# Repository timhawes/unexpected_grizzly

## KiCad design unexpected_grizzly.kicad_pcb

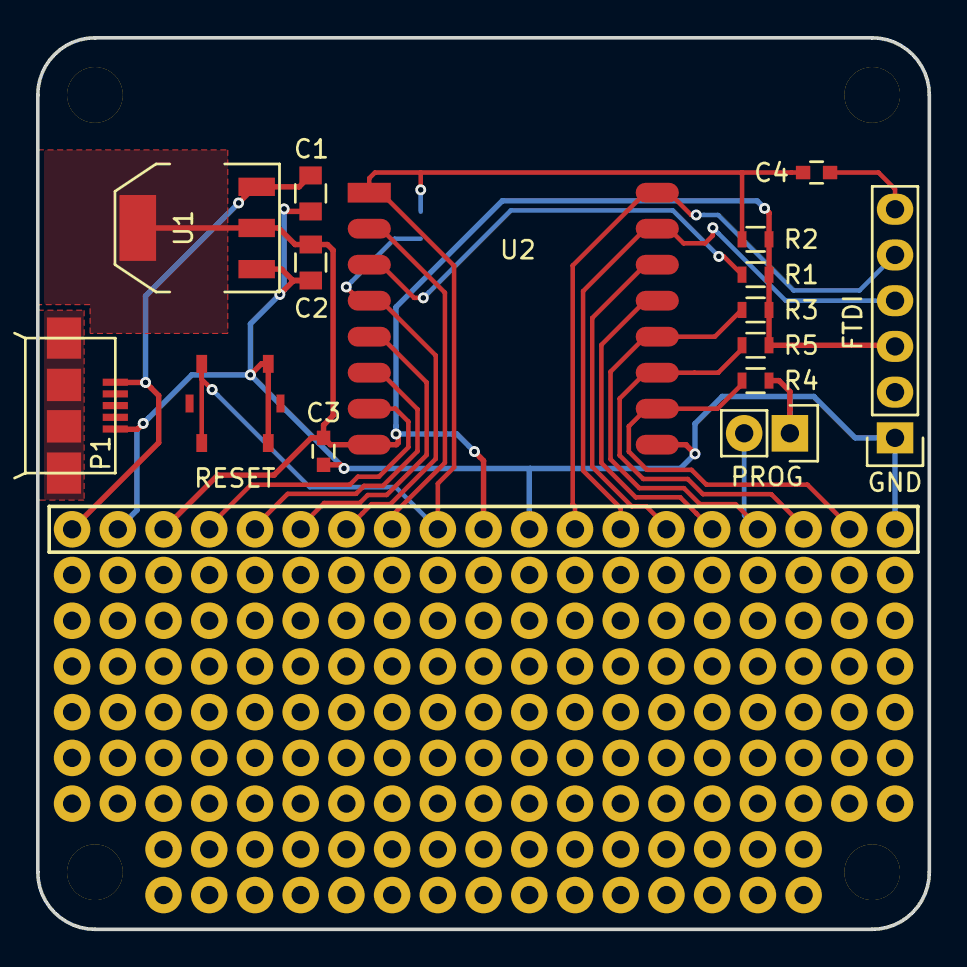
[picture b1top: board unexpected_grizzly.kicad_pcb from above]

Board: 2 copper layers, 49.5 x 49.5 mm, 17 parts (1 on the bottom side), 18 nets.

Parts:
C1, C2: 10uF; C_0805
C3, C4: 0.1uF; C_0603
JP1: PROG; Pin_Header_Straight_1x02
JP2: WAKE; R_0603
P1: USB; FCI_10104110_0001LF
P2: GPIO; Matrix_Row_19
P3: FTDI; Pin_Header_Straight_1x06
R1, R2, R3, R4, R5: 10K; R_0603
SW1: RESET; EVQPT5
U1: NCP1117ST33T3G; SOT-223
U2: ESP-12

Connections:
+3V3: C2.1, C3.1, P2.10, P2.17, P3.3, R1.1, R2.1, R3.1, R5.1, U1.2, U1.4, U2.8
+5V: C1.1, P1.1, P2.19, U1.3
ADC: P2.12, U2.2
GND: C1.2, C2.2, C3.2, JP1.1, P1.5, P2.1, P2.9, P2.18, P3.1, R4.1, SW1.2, U1.1, U2.9
GPIO0: JP1.2, P2.4, R3.2, U2.12
GPIO2: P2.3, R5.2, U2.11
GPIO4: P2.6, U2.14
GPIO5: P2.5, U2.13
GPIO12: P2.15, U2.6
GPIO13: P2.16, U2.7
GPIO14: P2.14, U2.5
GPIO15: P2.2, R4.2, U2.10
GPIO16: JP2.1, P2.13, U2.4
unnamed: C4.1, P3.6
unnamed: R1.2, U2.3
RESET: C4.2, JP2.2, P2.11, R2.2, SW1.1, U2.1
RX: P2.7, P3.4, U2.15
TX: P2.8, P3.5, U2.16

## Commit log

2015-11-27 Schematic PDF
2015-11-28 Correction to USB pinout. Other tidy-ups.
2015-11-29 Final V1
2015-11-29 Gerbers generated
